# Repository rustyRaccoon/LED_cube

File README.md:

# LED_cube
 4x4x4 LED cube that can display various patterns, based on 74HC595 and Attiny45

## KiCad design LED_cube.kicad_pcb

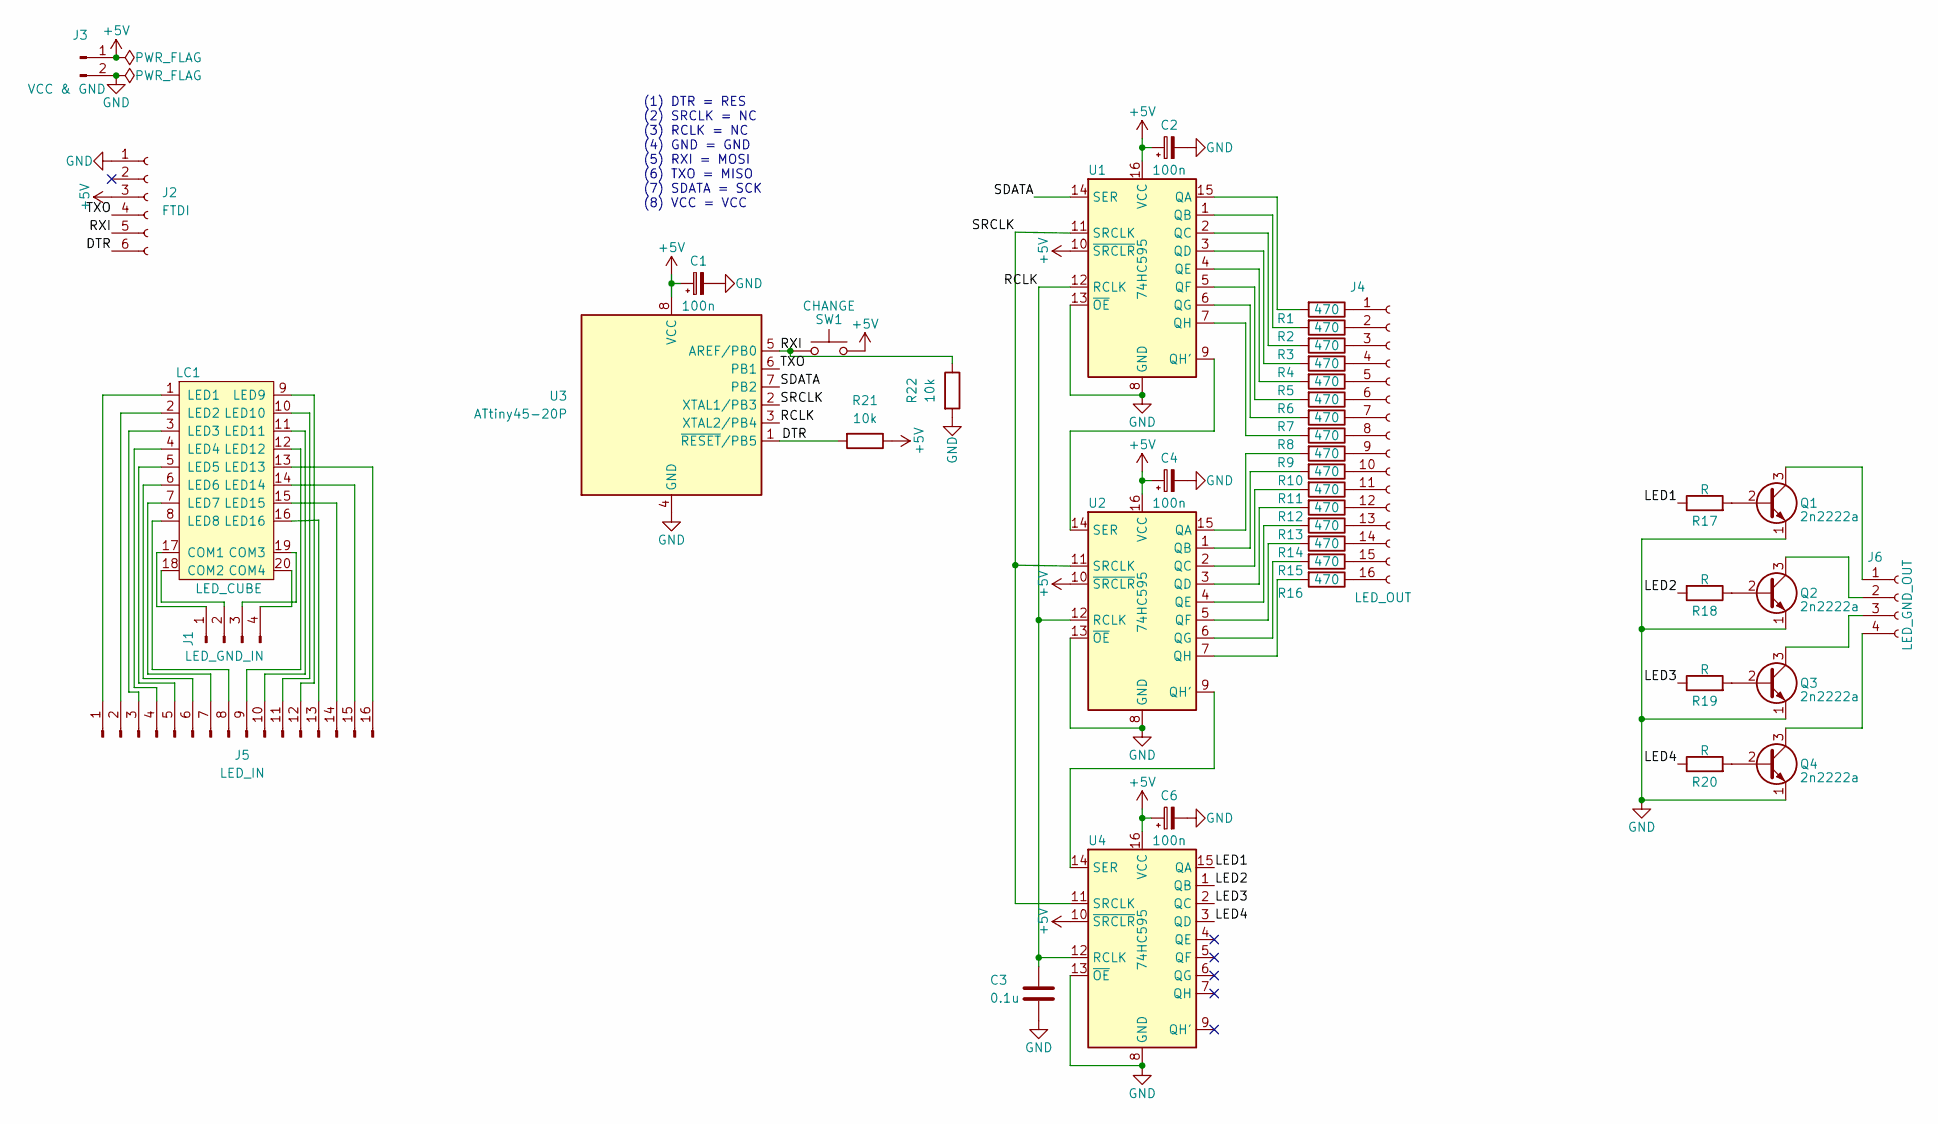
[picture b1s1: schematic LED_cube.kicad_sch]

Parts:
C1, C2, C4, C6: 100n; CP_Radial_D6.3mm_P2.50mm
C3: 0.1u; FakeSMD_C_Disc
J1: LED_GND_IN; PinHeader_1x04_P2.54mm_Vertical
J2: FTDI; PinSocket_1x06_P2.54mm_Horizontal
J3: VCC & GND; PinHeader_1x02_P2.54mm_Horizontal
J4: LED_OUT; PinHeader_1x16_P2.54mm_Vertical
J5: LED_IN; PinHeader_1x16_P2.54mm_Vertical
J6: LED_GND_OUT; PinHeader_1x04_P2.54mm_Vertical
LC1: LED_CUBE
Q1, Q2, Q3, Q4: 2n2222a; FakeSMD_TO-92-3_Vertical
R1, R2, R3, R4, R5, R6, R7, R8, R9, R10, R11, R12, R13, R14, R15, R16: 470; FakeSMD_R
R17, R18, R19, R20: R; R_Axial_DIN0207_L6.3mm_D2.5mm_P10.16mm_Horizontal
R21, R22: 10k; FakeSMD_R
SW1: CHANGE; PinHeader_1x02_P2.54mm_Vertical
U1, U2, U4: 74HC595; FakeSMD_DIP-16
U3: ATtiny45-20P; FakeSMD_DIP-8

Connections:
+5V: C1.1, C2.1, C4.1, C6.1, J2.3, J3.1, R21.1, SW1.2, U1.10 (~SRCLR), U1.16 (VCC), U2.10 (~SRCLR), U2.16 (VCC), U3.8 (VCC), U4.10 (~SRCLR), U4.16 (VCC)
/DTR: J2.6, R21.2, U3.1 (~RESET/PB5)
/LED1: R17.1, U4.15 (QA)
/LED2: R18.2, U4.1 (QB)
/LED3: R19.1, U4.2 (QC)
/LED4: R20.1, U4.3 (QD)
/RCLK: C3.1, U1.12 (RCLK), U2.12 (RCLK), U3.3 (XTAL2/PB4), U4.12 (RCLK)
/RXI: J2.5, R22.1, SW1.1, U3.5 (AREF/PB0)
/SDATA: U1.14 (SER), U3.7 (PB2)
/SRCLK: U1.11 (SRCLK), U2.11 (SRCLK), U3.2 (XTAL1/PB3), U4.11 (SRCLK)
/TXO: J2.4, U3.6 (PB1)
GND: C1.2, C2.2, C3.2, C4.2, C6.2, J2.1, J3.2, Q1.1 (E), Q2.1 (E), Q3.1 (E), Q4.1 (E), R22.2, U1.8 (GND), U1.13 (~OE), U2.8 (GND), U2.13 (~OE), U3.4 (GND), U4.8 (GND), U4.13 (~OE)
unnamed: J1.1, LC1.17 (COM1)
unnamed: J1.2, LC1.18 (COM2)
unnamed: J1.3, LC1.19 (COM3)
unnamed: J1.4, LC1.20 (COM4)
unnamed: J4.1, R1.1
unnamed: J4.2, R2.1
unnamed: J4.3, R3.1
unnamed: J4.4, R4.1
unnamed: J4.5, R5.1
unnamed: J4.6, R6.1
unnamed: J4.7, R7.1
unnamed: J4.8, R8.1
unnamed: J4.9, R9.1
unnamed: J4.10, R10.1
unnamed: J4.11, R11.1
unnamed: J4.12, R12.1
unnamed: J4.13, R13.1
unnamed: J4.14, R14.1
unnamed: J4.15, R15.1
unnamed: J4.16, R16.1
unnamed: J5.1, LC1.1 (LED1)
unnamed: J5.2, LC1.2 (LED2)
unnamed: J5.3, LC1.3 (LED3)
unnamed: J5.4, LC1.4 (LED4)
unnamed: J5.5, LC1.5 (LED5)
unnamed: J5.6, LC1.6 (LED6)
unnamed: J5.7, LC1.7 (LED7)
unnamed: J5.8, LC1.8 (LED8)
unnamed: J5.9, LC1.12 (LED12)
unnamed: J5.10, LC1.11 (LED11)
unnamed: J5.11, LC1.10 (LED10)
unnamed: J5.12, LC1.9 (LED9)
unnamed: J5.13, LC1.16 (LED16)
unnamed: J5.14, LC1.15 (LED15)
unnamed: J5.15, LC1.14 (LED14)
unnamed: J5.16, LC1.13 (LED13)
unnamed: J6.1, Q1.3 (C)
unnamed: J6.2, Q2.3 (C)
unnamed: J6.3, Q3.3 (C)
unnamed: J6.4, Q4.3 (C)
unnamed: Q1.2 (B), R17.2
unnamed: Q2.2 (B), R18.1
unnamed: Q3.2 (B), R19.2
unnamed: Q4.2 (B), R20.2
unnamed: R1.2, U1.15 (QA)
unnamed: R2.2, U1.1 (QB)
unnamed: R3.2, U1.2 (QC)
unnamed: R4.2, U1.3 (QD)
unnamed: R5.2, U1.4 (QE)
unnamed: R6.2, U1.5 (QF)
unnamed: R7.2, U1.6 (QG)
unnamed: R8.2, U1.7 (QH)
unnamed: R9.2, U2.15 (QA)
unnamed: R10.2, U2.1 (QB)
unnamed: R11.2, U2.2 (QC)
unnamed: R12.2, U2.3 (QD)
unnamed: R13.2, U2.4 (QE)
unnamed: R14.2, U2.5 (QF)
unnamed: R15.2, U2.6 (QG)
unnamed: R16.2, U2.7 (QH)
unnamed: U1.9 (QH'), U2.14 (SER)
unnamed: U2.9 (QH'), U4.14 (SER)

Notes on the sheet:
(1) DTR = RES (2) SRCLK = NC (3) RCLK = NC (4) GND = GND (5) RXI = MOSI (6) TXO = MISO (7) SDATA = SCK (8) VCC = VCC

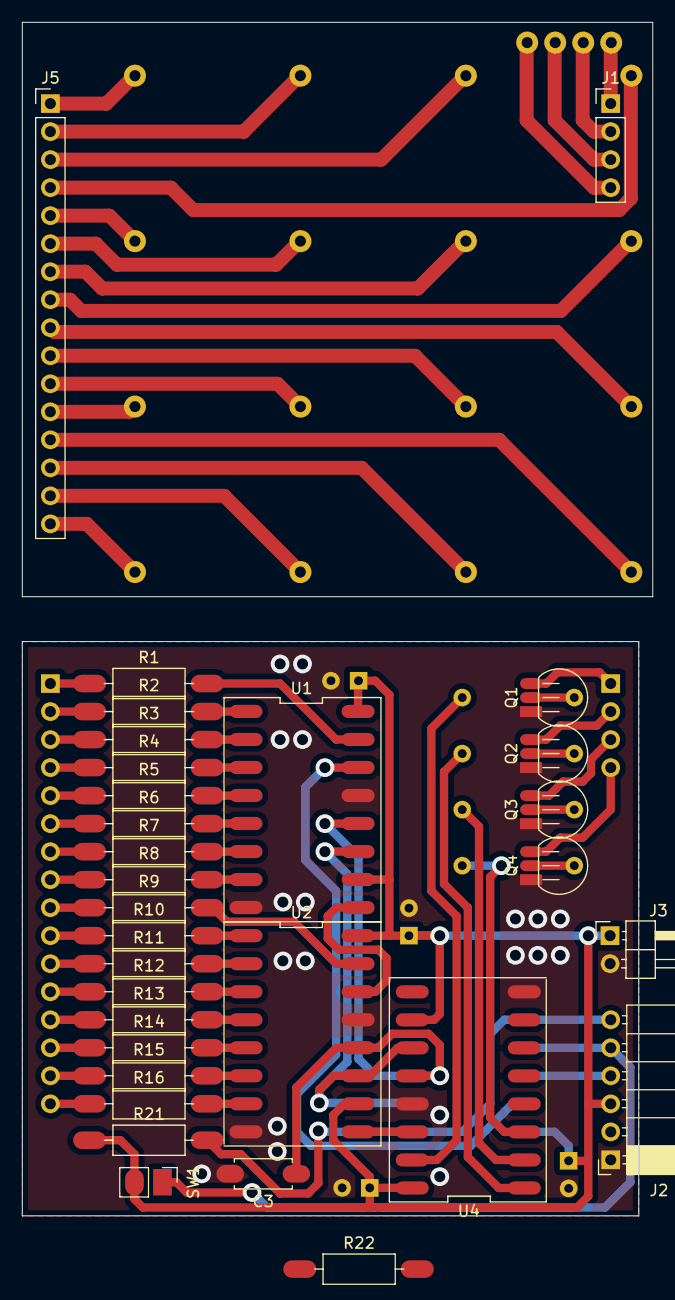
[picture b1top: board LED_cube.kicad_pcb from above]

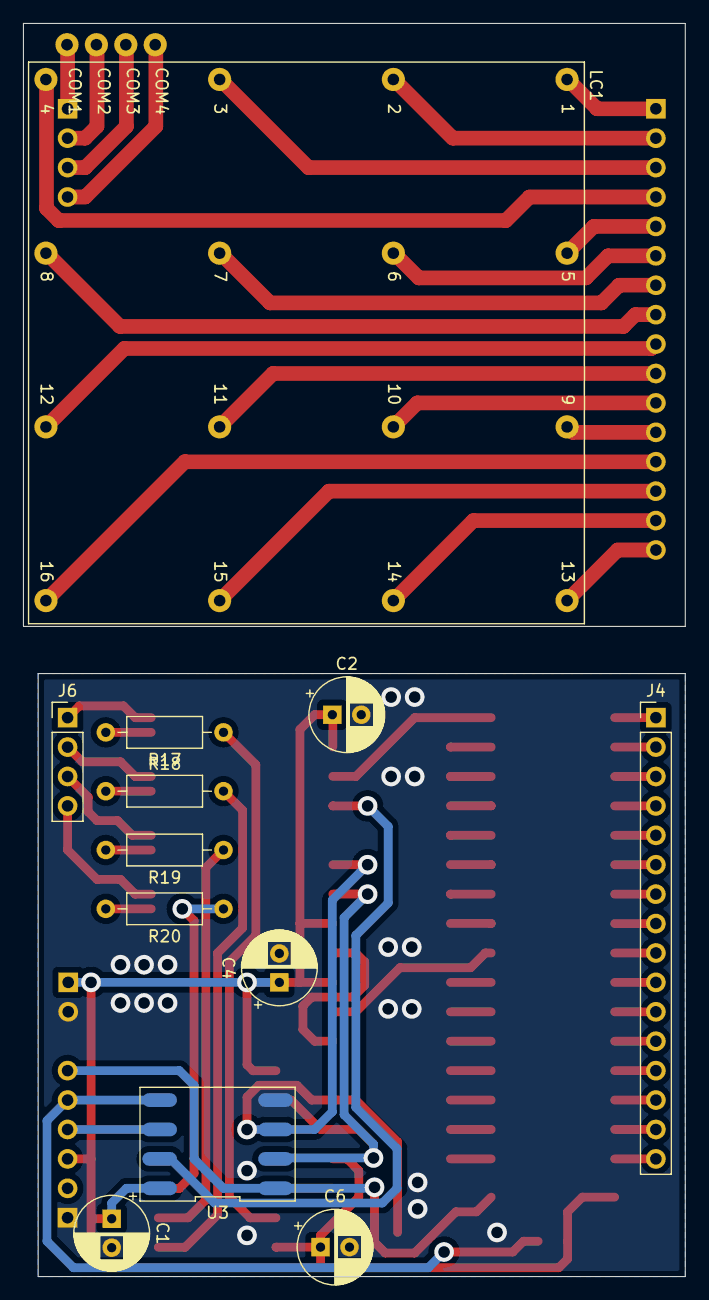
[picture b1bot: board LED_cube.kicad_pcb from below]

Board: 2 copper layers, 57.1 x 108.2 mm, 43 parts (12 on the bottom side), 74 nets.

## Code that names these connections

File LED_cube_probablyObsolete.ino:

/*
Author:		badBadger
Date:		2022-10-06
Version:	1.0
*/

// Pattern 0: Cycles through all LEDs consecutively, layer by layer
// Pattern 1: Every other LED is on (all layers are the same)
// Pattern 2: Every other LED is on (different for even/odd layers)
// Pattern 3: Cycles through all rows in each layer
// Pattern 4: Goes up one column of LEDs, then goes to the next one

//define attiny pins
#define BTN PB0
#define DATA PB2
#define CLK PB3
#define LATCH PB4

//changing variables
short data; //16-bits for 16 LEDs per layer
byte layer; //lower 4 bits for layers, upper 4 bits for buffer
uint16_t delayLED; //wait time between LEDs [ms]
uint32_t lastTime; //last timestamp for delay
uint8_t pattern;
uint8_t LED_counter;
uint8_t layer_counter;
volatile bool buttonPressed;
volatile bool previousState;
volatile uint8_t switchCheck;

void setup()
{
  cli(); // Disable interrupts during setup
  
  pinMode(BTN, INPUT); // Set interrupt pin as input w/ internal pullup
  pinMode(DATA, OUTPUT); // Set serial data as output
  pinMode(CLK, OUTPUT); // Set shift register clock as output
  pinMode(LATCH, OUTPUT); // Set output register (latch) clock as output

  // set up Timer 1
  GTCCR |= (1 << PSR1); // Reset prescaler
  TCCR1 = 0;
  TCCR1 |= (1 << CTC1) | (1 << CS12) | (1 << CS11) | (1 << CS10); // Enable counter on compare match and set prescaler to 64
  TCNT1 = 0; // Zero the timer
  OCR1C = 49; // set compare time to ~200us -> 1/(1e6 / 64 / (49 + 1)) = 200us
  TIMSK |= (1 << OCIE1A); // compare interrupt enable of matchA

  //default conditions
  data = 0b0000000000000001;
  layer = 0b00000001;
  delayLED = 500;
  lastTime = 0;
  pattern = 0;
  LED_counter = 0;
  layer_counter = 0;
  buttonPressed = false;
  sei(); //enable interrupts after setup
}

void loop()
{
  if(buttonPressed){
    changePattern();
  }

  if((millis()-lastTime)>=delayLED){ //if delay time is over...
    //...do the next iteration of things
    lastTime = millis(); //update timestamp
    digitalWrite(LATCH, 0); //Set latch pin LOW so nothing gets shifted out
    shiftOutLayer(DATA, CLK, layer); //Shift out information which layer is on
    data = getPattern(pattern); //Choose  pattern for layer
    shiftOutShort(DATA, CLK, data); //Shift out LED states in that layer
    digitalWrite(LATCH, 1); //sent everything out in parallel
  }
} 

ISR(TIMER1_COMPA_vect){  
  static uint8_t count = 0; // Counter for number of equal states
  static uint8_t button_state = 0; // Keeps track of current (debounced) state
  uint8_t current_state = PINB & (1 << PINB0) != 0; // Check if button is high or low for the moment
  
  if (current_state != button_state) {
    count++; // Button state is about to be changed, increase counter
    if (count >= 4) {
      button_state = current_state; // The button have not bounced for four checks, change state
        if (current_state != 0) {
          buttonPressed = true; // If the button was pressed (not released), tell main so
        }
      count = 0;
    }
  }
  else{
    count = 0; // Reset counter
  }
}

short getPattern(int pattern){
  short output = 0b0000000000000000;
  
  switch(pattern){
    //just cycles through all LEDs in each layer
    case 0:
      //Set delays for pattern
      //delayLED = 500;
    
      //Set LED states
      if(LED_counter == 17){
        output = 0000000000000001;
        LED_counter = 0;
      }
      else{
        output = 0b0000000000000001 << LED_counter;
      }
    
      if(LED_counter == 16){
        changeLayer();
      }
    
      LED_counter++;
      break;
    
    //every other LED is on (same for all layers)
    case 1:
      //Set delays for pattern
      delayLED = 500;
    
      //Set LED states
      output = 0b1010101010101010;
    
      changeLayer();
      break;
    
    //every other LED is on (mirrored in even layers)
    case 2:
      //Set delays for pattern
      //delayLED = 500;
    
      //Set LED states
      if(layer%2 == 0){
        output = 0b0101010101010101;
      }
      else{
        output = 0b1010101010101010;
      }
    
      changeLayer();
      break;
    
    //cycles through all rows in each layer
    case 3:
      //Set delays for pattern
      //delayLED = 500;
    
      //Set LED states
      if(LED_counter == 5){
      	output = 0b0000000000001111;
        LED_counter = 0;
      }
      else{
		output = 0b0000000000001111 << LED_counter*4;
      }
    
      if(LED_counter == 4){
        changeLayer();
      }
    
      LED_counter++;
      break;
    
    case 4:
      //Set delays for pattern
      //delayLED = 500;
    
      //Set LED states
      if(layer_counter == 4){
        layer_counter = 0;
        LED_counter++;
      }
         
      if(LED_counter == 16){
        LED_counter = 0;
      }
      
      output = 0b0000000000000001 << LED_counter;
      changeLayer();
      layer_counter++;
      break;
      
    
    //just defaults to all LEDs off
    default:
      output = 0b0000000000000000;
      break;
   }

  return output;
}

// Switch to the next layer, or circle back to the first one
void changeLayer(){
  if(layer & 0b00001000){
    layer = 0b0001;
  }
  else{
    layer = layer << 1;
  }
}

// Changes to the next pattern after interrupt
void changePattern(){
  //reset pattern change flag
  buttonPressed = false;
  
  //check if last pattern is reached
  if(pattern < 4){
    pattern +=1;
  }
  else{
    pattern = 0;
  }
    
  layer = 1;
  LED_counter = 0;
}

// This shifts 4 bits out MSB first, on the rising edge of the clock.
void shiftOutLayer(int dataPin, int clockPin, byte layer){
  int i = 0;
  int pinState = 0;
  
  //clear everything just in case
  digitalWrite(dataPin, 0);
  digitalWrite(clockPin, 0);

  for(i=3; i>=0; i--){
    digitalWrite(clockPin,0);
    
    if(layer & (1<<i)){
      pinState = 1;
    }
    else{
      pinState = 0;
    }
    
    digitalWrite(dataPin, pinState);
    digitalWrite(clockPin,1);
    digitalWrite(dataPin, 0);
  }
  
  digitalWrite(clockPin,0);
}

// This shifts 16 bits out MSB first, on the rising edge of the clock.
void shiftOutShort(int dataPin, int clockPin, short toBeSent){
  int i=0;
  int pinState = 0;
  
  //Clear everything out just in case
  digitalWrite(dataPin, 0);
  digitalWrite(clockPin, 0);

  //Loop through bits in the data bytes
  //COUNTING DOWN in the for loop so that %00000001 or "1"
  //will go through such that it will be pin Q0 that lights.
  for(i=15; i>=0; i--){
    digitalWrite(clockPin, 0);
    //if the value passed to myDataOut AND a bitmask result
    //in true then set pinState to 1
    if(toBeSent & (1<<i)){
      pinState = 1;
    }
    else{
      pinState = 0;
    }
    
    digitalWrite(dataPin, pinState); //Sets the pin to HIGH or LOW depending on pinState
    digitalWrite(clockPin, 1); //Shifts bits on upstroke of clock pin
    digitalWrite(dataPin, 0); //Zero the data pin after shift to prevent bleed through
  }
  digitalWrite(clockPin, 0); //Stop shifting
}
